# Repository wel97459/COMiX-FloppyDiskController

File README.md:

# COMiX-FloppyDiskController
Floppy Disk Controller for the COMiX-35 computer utilizing three GAL22v11's

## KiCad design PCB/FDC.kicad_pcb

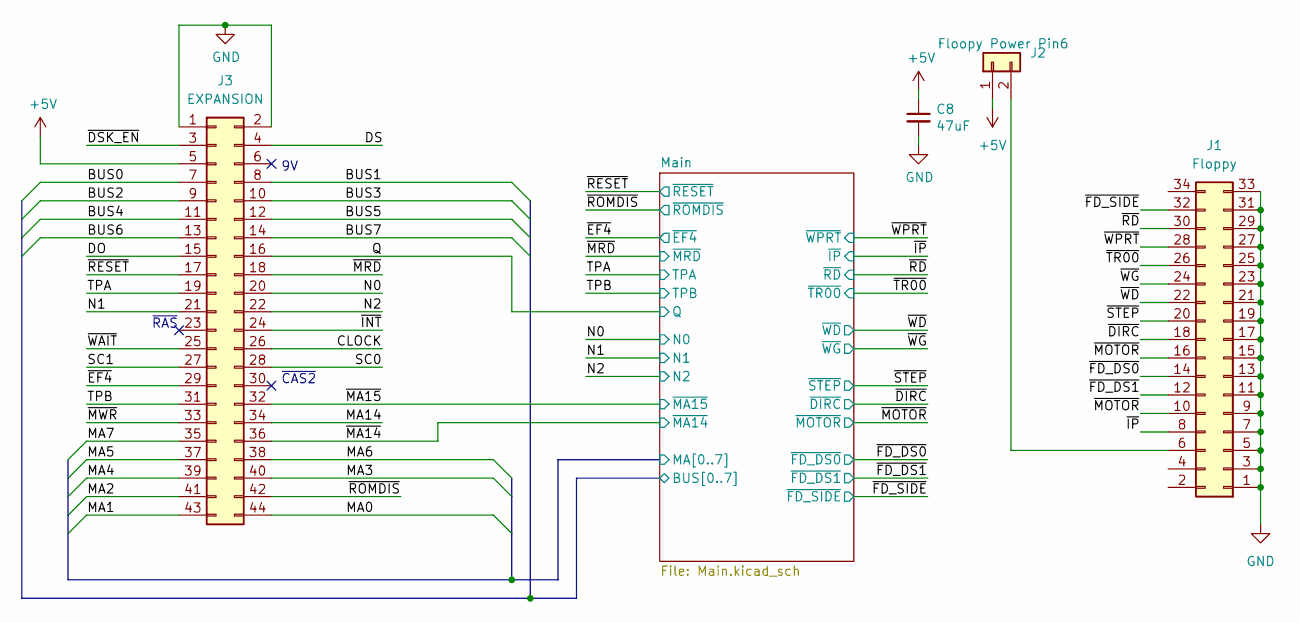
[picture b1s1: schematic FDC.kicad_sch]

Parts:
C8: 47uF; C_Radial_D4.0mm_H7.0mm_P1.50mm; Mouser 581-SA105E104M
J1: Floppy; PinHeader_2x17_P2.54mm_Vertical
J2: Floopy Power Pin6; PinHeader_1x02_P2.54mm_Vertical
J3: EXPANSION; COMiX35_Edge_Card_Connector_22x2

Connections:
+5V: C8.1, J2.1, J3.5; also elsewhere on the board
/CLOCK: J3.26
/DO: J3.15
/DS: J3.4
/MA14: J3.34
/Main/BUS0: J3.7; also elsewhere on the board
/Main/BUS1: J3.8; also elsewhere on the board
/Main/BUS2: J3.9; also elsewhere on the board
/Main/BUS3: J3.10; also elsewhere on the board
/Main/BUS4: J3.11; also elsewhere on the board
/Main/BUS5: J3.12; also elsewhere on the board
/Main/BUS6: J3.13; also elsewhere on the board
/Main/BUS7: J3.14; also elsewhere on the board
/Main/MA0: J3.44; also elsewhere on the board
/Main/MA1: J3.43; also elsewhere on the board
/Main/MA2: J3.41; also elsewhere on the board
/Main/MA3: J3.40; also elsewhere on the board
/Main/MA4: J3.39; also elsewhere on the board
/Main/MA5: J3.37; also elsewhere on the board
/Main/MA6: J3.38; also elsewhere on the board
/Main/MA7: J3.35; also elsewhere on the board
/N0: J3.20; also elsewhere on the board
/N1: J3.21; also elsewhere on the board
/N2: J3.22; also elsewhere on the board
/Q: J3.16; also elsewhere on the board
/SC0: J3.28
/SC1: J3.27
/TPA: J3.19; also elsewhere on the board
/TPB: J3.31; also elsewhere on the board
/~DIRC: J1.18; also elsewhere on the board
/~DSK_EN: J3.3
/~EF4: J3.29; also elsewhere on the board
/~FD_DS0: J1.14; also elsewhere on the board
/~FD_DS1: J1.12; also elsewhere on the board
/~FD_SIDE: J1.32; also elsewhere on the board
/~INT: J3.24
/~IP: J1.8; also elsewhere on the board
/~MA14: J3.36; also elsewhere on the board
/~MA15: J3.32; also elsewhere on the board
/~MOTOR: J1.10, J1.16; also elsewhere on the board
/~MRD: J3.18; also elsewhere on the board
/~MWR: J3.33
/~RD: J1.30; also elsewhere on the board
/~RESET: J3.17; also elsewhere on the board
/~ROMDIS: J3.42; also elsewhere on the board
/~STEP: J1.20; also elsewhere on the board
/~TR00: J1.26; also elsewhere on the board
/~WAIT: J3.25
/~WD: J1.22; also elsewhere on the board
/~WG: J1.24; also elsewhere on the board
/~WPRT: J1.28; also elsewhere on the board
GND: C8.2, J1.1, J1.3, J1.5, J1.7, J1.9, J1.11, J1.13, J1.15, J1.17, J1.19, J1.21, J1.23, J1.25, J1.27, J1.29, J1.31, J1.33, J3.1, J3.2; also elsewhere on the board
unnamed: J1.6, J2.2

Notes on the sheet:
~{CAS2}
~{RAS}

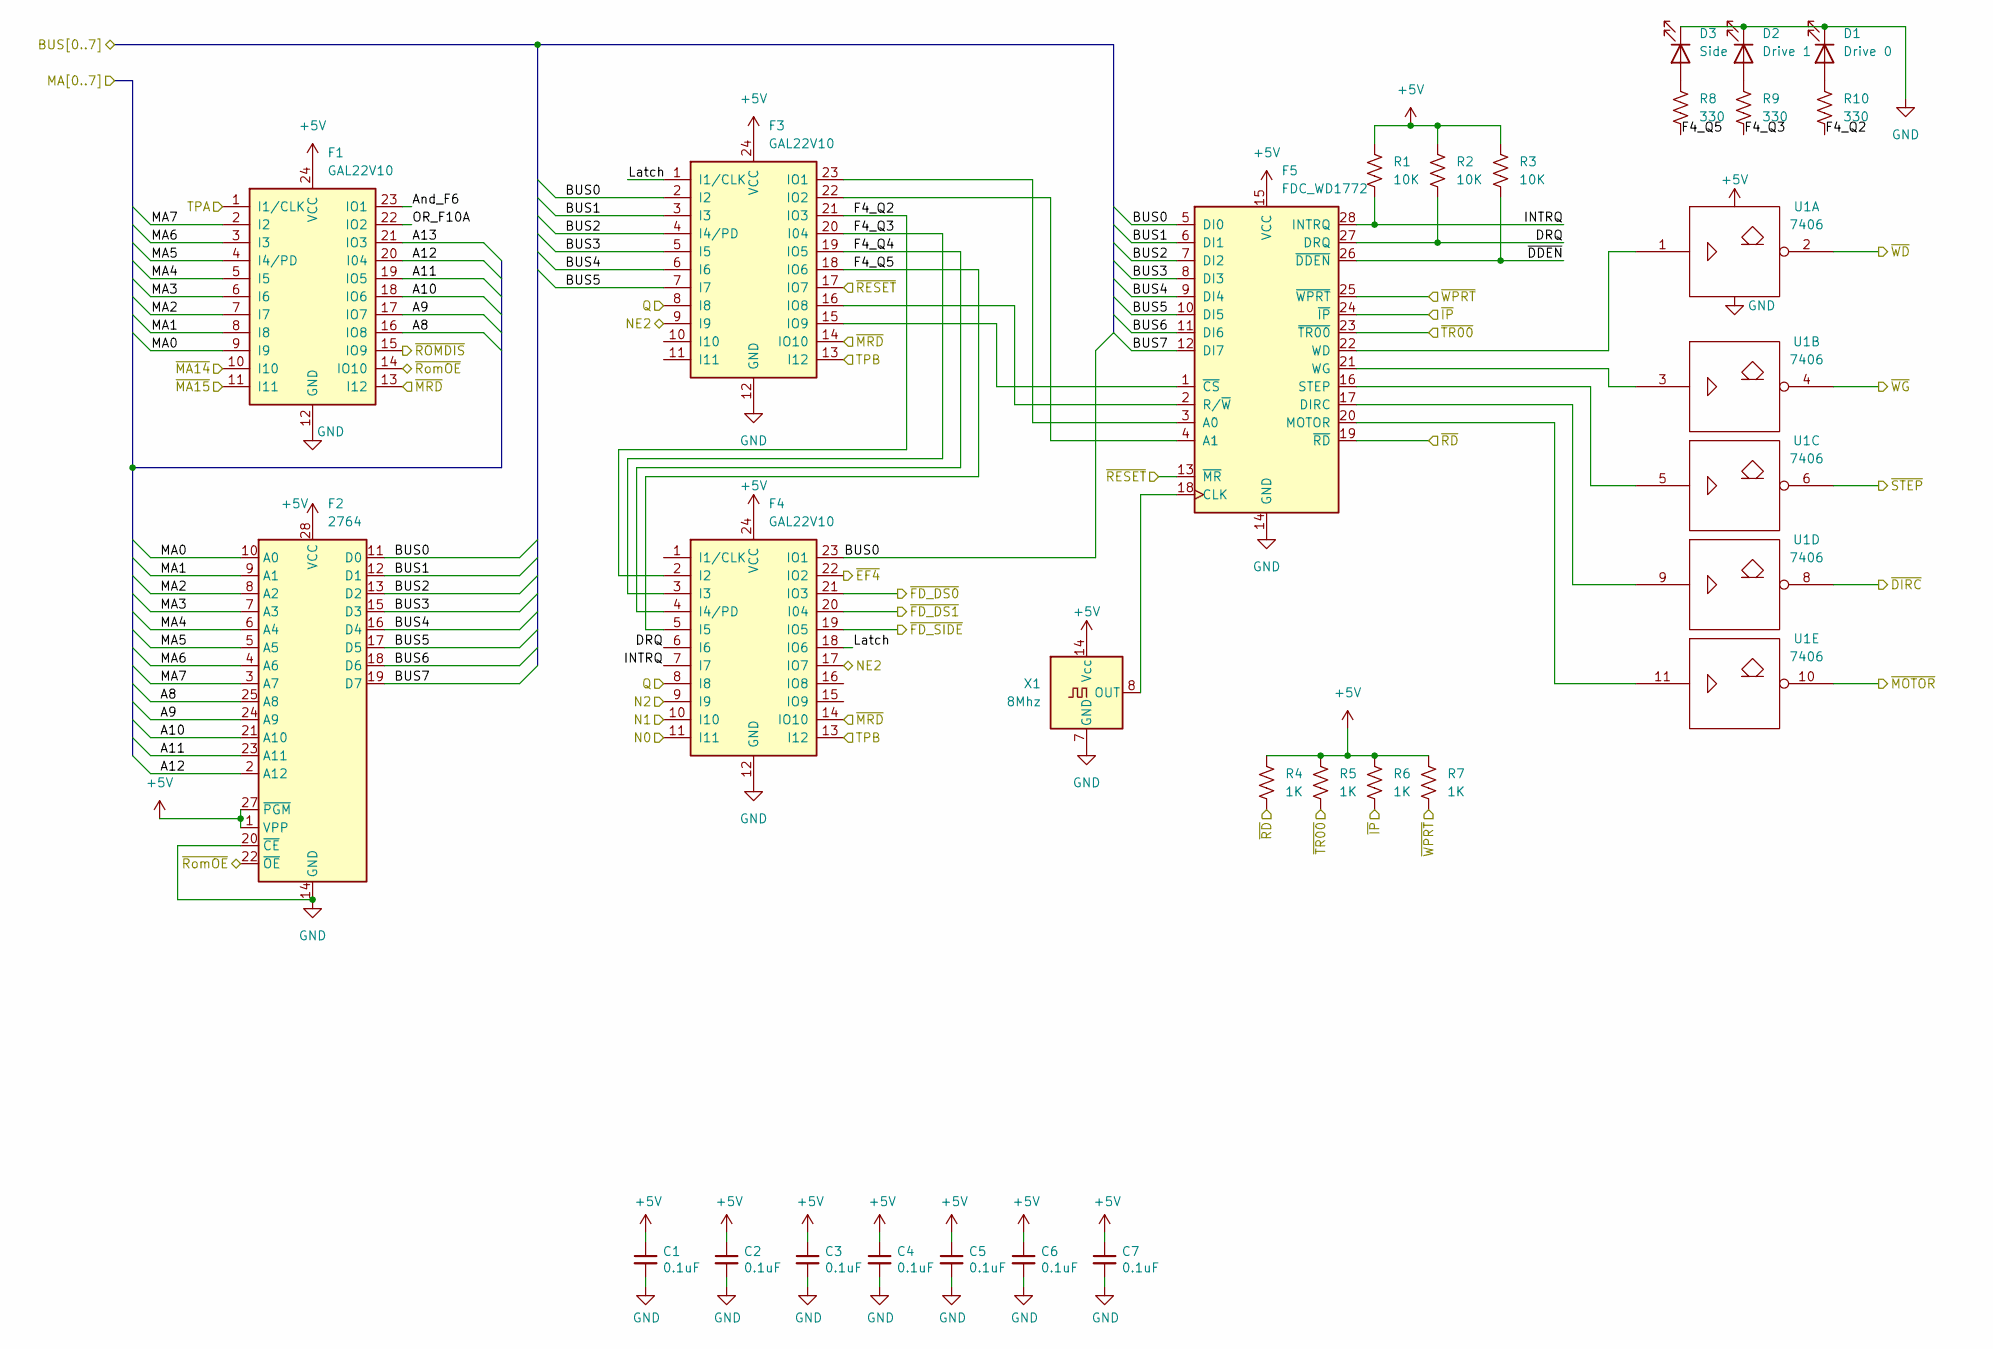
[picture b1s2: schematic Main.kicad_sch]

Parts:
C1, C2, C3, C4, C5, C6, C7: 0.1uF; C_Disc_D5.0mm_W2.5mm_P2.50mm; Mouser 581-SA105E104M
D1: Drive 0; LED_D5.0mm
D2: Drive 1; LED_D5.0mm
D3: Side; LED_D5.0mm
F1, F3, F4: GAL22V10; DIP-24_W7.62mm
F2: 2764; DIP-28_W15.24mm
F5: FDC_WD1772; DIP-28_W15.24mm
R1, R2, R3: 10K; R_Axial_DIN0204_L3.6mm_D1.6mm_P11.43mm_Horizontal
R4, R5, R6, R7: 1K; R_Axial_DIN0204_L3.6mm_D1.6mm_P11.43mm_Horizontal
R8, R9, R10: 330; R_Axial_DIN0204_L3.6mm_D1.6mm_P11.43mm_Horizontal
U1: 7406; DIP-14_W7.62mm
X1: 8Mhz; Oscillator_DIP-14

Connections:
+5V: C1.1, C2.1, C3.1, C4.1, C5.1, C6.1, C7.1, F1.24 (VCC), F2.1 (VPP), F2.27 (~PGM), F2.28 (VCC), F3.24 (VCC), F4.24 (VCC), F5.15 (VCC), R1.2, R2.1, R3.1, R4.2, R5.2, R6.2, R7.2, U1.14 (Vcc), X1.14 (Vcc); also elsewhere on the board
/Main/A8: F1.16 (IO8), F2.25 (A8)
/Main/A9: F1.17 (IO7), F2.24 (A9)
/Main/A10: F1.18 (IO6), F2.21 (A10)
/Main/A11: F1.19 (IO5), F2.23 (A11)
/Main/A12: F1.20 (I04), F2.2 (A12)
/Main/A13: F1.21 (IO3)
/Main/And_F6: F1.23 (IO1)
/Main/BUS0: F2.11 (D0), F3.2 (I2), F4.23 (IO1), F5.5 (DI0); also elsewhere on the board
/Main/BUS1: F2.12 (D1), F3.3 (I3), F5.6 (DI1); also elsewhere on the board
/Main/BUS2: F2.13 (D2), F3.4 (I4/PD), F5.7 (DI2); also elsewhere on the board
/Main/BUS3: F2.15 (D3), F3.5 (I5), F5.8 (DI3); also elsewhere on the board
/Main/BUS4: F2.16 (D4), F3.6 (I6), F5.9 (DI4); also elsewhere on the board
/Main/BUS5: F2.17 (D5), F3.7 (I7), F5.10 (DI5); also elsewhere on the board
/Main/BUS6: F2.18 (D6), F5.11 (DI6); also elsewhere on the board
/Main/BUS7: F2.19 (D7), F5.12 (DI7); also elsewhere on the board
/Main/DRQ: F4.6 (I6), F5.27 (DRQ), R2.2
/Main/F4_Q2: F3.21 (IO3), F4.2 (I2), R10.1
/Main/F4_Q3: F3.20 (I04), F4.3 (I3), R9.1
/Main/F4_Q4: F3.19 (IO5), F4.4 (I4/PD)
/Main/F4_Q5: F3.18 (IO6), F4.5 (I5), R8.1
/Main/INTRQ: F4.7 (I7), F5.28 (INTRQ), R1.1
/Main/Latch: F3.1 (I1/CLK), F4.18 (IO6)
/Main/MA0: F1.9 (I9), F2.10 (A0); also elsewhere on the board
/Main/MA1: F1.8 (I8), F2.9 (A1); also elsewhere on the board
/Main/MA2: F1.7 (I7), F2.8 (A2); also elsewhere on the board
/Main/MA3: F1.6 (I6), F2.7 (A3); also elsewhere on the board
/Main/MA4: F1.5 (I5), F2.6 (A4); also elsewhere on the board
/Main/MA5: F1.4 (I4/PD), F2.5 (A5); also elsewhere on the board
/Main/MA6: F1.3 (I3), F2.4 (A6); also elsewhere on the board
/Main/MA7: F1.2 (I2), F2.3 (A7); also elsewhere on the board
/Main/NE2: F3.9 (I9), F4.17 (IO7)
/Main/OR_F10A: F1.22 (IO2)
/Main/~DDEN: F5.26 (~DDEN), R3.2
/Main/~RomOE: F1.14 (IO10), F2.22 (~OE)
/N0: F4.11 (I11); also elsewhere on the board
/N1: F4.10 (I10); also elsewhere on the board
/N2: F4.9 (I9); also elsewhere on the board
/Q: F3.8 (I8), F4.8 (I8); also elsewhere on the board
/TPA: F1.1 (I1/CLK); also elsewhere on the board
/TPB: F3.13 (I12), F4.13 (I12); also elsewhere on the board
/~DIRC: U1.8; also elsewhere on the board
/~EF4: F4.22 (IO2); also elsewhere on the board
/~FD_DS0: F4.21 (IO3); also elsewhere on the board
/~FD_DS1: F4.20 (I04); also elsewhere on the board
/~FD_SIDE: F4.19 (IO5); also elsewhere on the board
/~IP: F5.24 (~IP), R6.1; also elsewhere on the board
/~MA14: F1.10 (I10); also elsewhere on the board
/~MA15: F1.11 (I11); also elsewhere on the board
/~MOTOR: U1.10; also elsewhere on the board
/~MRD: F1.13 (I12), F3.14 (IO10), F4.14 (IO10); also elsewhere on the board
/~RD: F5.19 (~RD), R4.1; also elsewhere on the board
/~RESET: F3.17 (IO7), F5.13 (~MR); also elsewhere on the board
/~ROMDIS: F1.15 (IO9); also elsewhere on the board
/~STEP: U1.6; also elsewhere on the board
/~TR00: F5.23 (~TR00), R5.1; also elsewhere on the board
/~WD: U1.2; also elsewhere on the board
/~WG: U1.4; also elsewhere on the board
/~WPRT: F5.25 (~WPRT), R7.1; also elsewhere on the board
GND: C1.2, C2.2, C3.2, C4.2, C5.2, C6.2, C7.2, D1.1 (K), D2.1 (K), D3.1 (K), F1.12 (GND), F2.14 (GND), F2.20 (~CE), F3.12 (GND), F4.12 (GND), F5.14 (GND), U1.7 (Gnd), X1.7 (GND); also elsewhere on the board
unnamed: D1.2 (A), R10.2
unnamed: D2.2 (A), R9.2
unnamed: D3.2 (A), R8.2
unnamed: F3.23 (IO1), F5.3 (A0)
unnamed: F3.22 (IO2), F5.4 (A1)
unnamed: F3.16 (IO8), F5.2 (R/~W)
unnamed: F3.15 (IO9), F5.1 (~CS)
unnamed: F5.18 (CLK), X1.8 (OUT)
unnamed: F5.17 (DIRC), U1.9
unnamed: F5.20 (MOTOR), U1.11
unnamed: F5.16 (STEP), U1.5
unnamed: F5.22 (WD), U1.1
unnamed: F5.21 (WG), U1.3

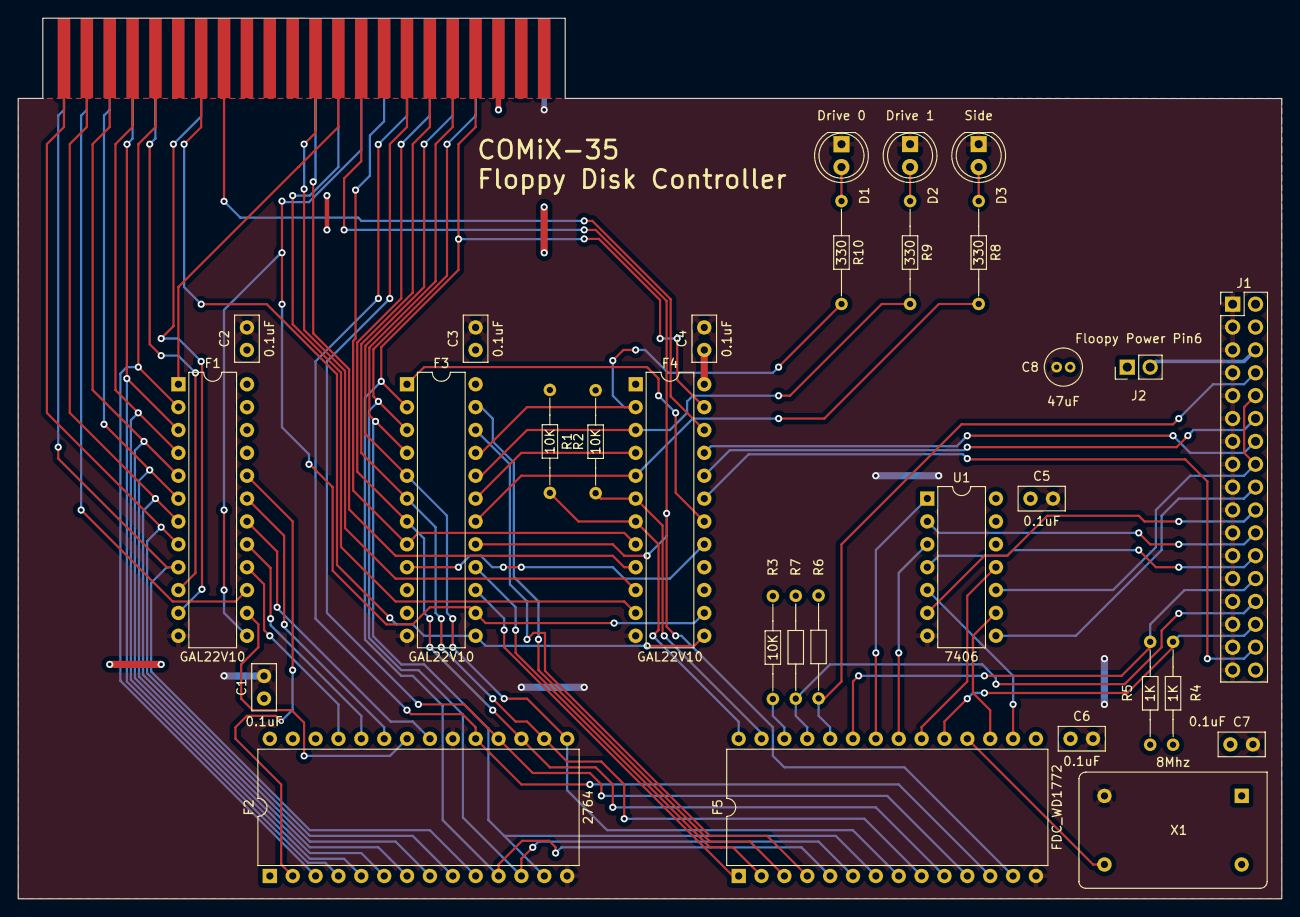
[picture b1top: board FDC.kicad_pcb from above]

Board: 2 copper layers, 140.3 x 97.8 mm, 31 parts (1 on the bottom side), 71 nets.

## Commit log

2023-12-06 adding KiCad Files
2023-12-06 Adding GAl Code
2023-12-25 Added Pull-ups to WD177X
